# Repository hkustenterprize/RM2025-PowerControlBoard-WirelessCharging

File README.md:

<div align="center">

# RM2025-超级电容与无线充电系统开源
## 香港科技大学ENTERPRIZE战队

</div>

> 论坛链接：https://bbs.robomaster.com/article/761385?source=8

以下为复制论坛内容

大家好呀，RM2025的超级电容和无线充电的开源报告终于写完了，这套前前后后做了三四个月，最后在用在了所有上场的车上（无线充只有步兵和英雄有），场上没出过什么问题，很稳定。硬件上与上一代开源没有很大变动，主要的改动是超级电容换了**峰值电流内环**，然后与无线充电进行了融合，放到了一个MCU上去控。虽然有一些缺陷和不足但是总体效果还可以，希望可以帮到大家。如果大家有任何有疑问或者发现有问题的地方欢迎随时联系！

> 欢迎加入开源交流QQ群：581184202

发射端/功控板硬件、功控板代码：xzm
> 联系方式：微信 xianziming0531，邮箱 zxianaa@connect.ust.hk

发射端代码：zzy
> 联系方式：微信 baoqi-zhong，邮箱 zzhongas@connect.ust.hk

## 前言

因为峰值电流调试起来比较复杂，也比较麻烦，所以大家有需要还是建议优先参考我们24年/23年的开源，这两版电容都是可以保证稳定的，24年的开源基本上板子做出了烧个代码就能用了。

硬件上整体改动不大，也是分了上下板的设计，下板加了一个用来无线充电的数控Buck，MCU换成了G474，为了峰值电流改了采样电阻的位置，然后根据写23赛季开源的学长的建议改了一下实现上管常开的方式，具体的东西都写在开源报告里了。

整体上场的效果还是不错的，电容响应很快，无线充电功率传输和反向通讯表现也很稳定（可惜复活赛输太快了没在比赛时充），今后有机会也会补充更多资料。无线充效果展示可以看 https://bbs.robomaster.com/article/760961 里面的视频。

## 工程文件

使用 KiCAD 8.0设计，可以点击下面的链接用 kicanvas 在线预览。

功控板上板：[<u>**点击预览**</u>](https://kicanvas.org/?github=https%3A%2F%2Fgithub.com%2Fhkustenterprize%2FRM2025-PowerControlBoard-WirelessCharging%2Ftree%2Fmain%2FPowerControl_PCM_V0.1_Control)

功控板下板： [<u>**点击预览**</u>](https://kicanvas.org/?github=https%3A%2F%2Fgithub.com%2Fhkustenterprize%2FRM2025-PowerControlBoard-WirelessCharging%2Ftree%2Fmain%2FPowerControl_PCM_V0.1_Power )

无线充电发射端： [<u>**点击预览**</u>](https://kicanvas.org/?github=https%3A%2F%2Fgithub.com%2Fhkustenterprize%2FRM2025-PowerControlBoard-WirelessCharging%2Ftree%2Fmain%2FWirelessCharger_V0.1 )

无线充电接收端线圈： [<u>**点击预览**</u>](https://kicanvas.org/?github=https%3A%2F%2Fgithub.com%2Fhkustenterprize%2FRM2025-PowerControlBoard-WirelessCharging%2Ftree%2Fmain%2FPowerControlBoard_RXCoil_V0.1 )

## 开源报告

见“技术报告” 文件夹

[**技术报告 PDF**](https://github.com/hkustenterprize/RM2025-PowerControlBoard-WirelessCharging/blob/main/%E6%8A%80%E6%9C%AF%E6%8A%A5%E5%91%8A/RM2025%E8%B6%85%E7%BA%A7%E7%94%B5%E5%AE%B9%E4%B8%8E%E6%97%A0%E7%BA%BF%E5%85%85%E7%94%B5%E7%B3%BB%E7%BB%9F%E6%8A%80%E6%9C%AF%E6%8A%A5%E5%91%8A.pdf)

[**省流版 PDF**](https://github.com/hkustenterprize/RM2025-PowerControlBoard-WirelessCharging/blob/main/%E6%8A%80%E6%9C%AF%E6%8A%A5%E5%91%8A/%E7%9C%81%E6%B5%81%E7%89%88.pdf)

## 代码

功控板（超级电容+无线充电接收端）：待整理和测试，9月初整理过后的代码测好后开源

无线充电发射端：待整理，近期开源

## 相关开源
无线充电站机械结构：[ **【RM2025-无线充电站机械结构思路分享】香港科技大学ENTERPRIZE战队** ](https://bbs.robomaster.com/article/760961)

电容组：[**【RM2025-超小体积1980J电容组开源】香港科技大学ENTERPRIZE战队**](https://bbs.robomaster.com/article/760959)

## 复刻/已知问题/使用注意事项

1. 如果使用无线充电需要在功率控制板下板 无线充Buck的上管并联一个大功率肖特基二极管
2. 无线充电发射端的峰值检测二极管需要替换为肖特基二极管并联或其他快恢复二极管
3. 无线充电发射端的谐振电感需要自己绕，铁粉芯磁芯+利兹线
4. 使用手册和其他注意事项待完善，如遇问题欢迎随时联系

## 参考资料
1. 【RM2024超级电容控制器硬件+软件完全开源】 (史上最详细的开源！)香港科技大学ENTERPRIZE战队 https://bbs.robomaster.com/article/54127

2. 【RM2023-数控超级电容方案开源】香港科技大学-ENTERPRIZE战队 https://bbs.robomaster.com/article/9452

3. STM32 AN5306: Operational Amplifier (OPAMP) usage in STM32G4 Series

4. STM32 RM0440: STM32G4 series advanced Arm®-based 32-bit MCUs

5. STM32 AN5497: Introduction to the buck current mode with the B-G474E-DPOW1 Discovery kit（重要）

6. STM32 AN4539: HRTIM cookbook 

7. Qi Specification: Communications Physical Layer, Version 2.0 April 2023 

8. NXP AN4701: Demodulating Communication Signals of Qi-Compliant Low-Power Wireless Charger Using MC56F8006 DSC
STM32G474xB STM32G474xC STM32G474xE Datasheet 

## 致谢
感谢 ENTERPRIZE 战队硬件组学长 JYC RY OFR 为硬件部门打下的坚实基础，并在本赛季为超级电容与无线充电系统的设计调试中提供了巨大帮助

感谢 ENTERPRIZE 战队硬件组队员 ZZY 承担了大部分构建、调试发射端代码的工作

感谢机械组SJY帮忙画的保护外壳

感谢吉林大学、中国石油大学（华东）、华南理工大学在交流中分享的宝贵经验

非常感谢各位对香港科技大学 ENTERPRIZE 战队开源项目的关注与支持，若您在机器人设计过程中受益于我们的项目，恳请在开源引用中注明我们的项目来源。你们的支持是我们不断前行的动力。让我们携手共建一个鼓励创新、协作与超越的 RM 开源生态。

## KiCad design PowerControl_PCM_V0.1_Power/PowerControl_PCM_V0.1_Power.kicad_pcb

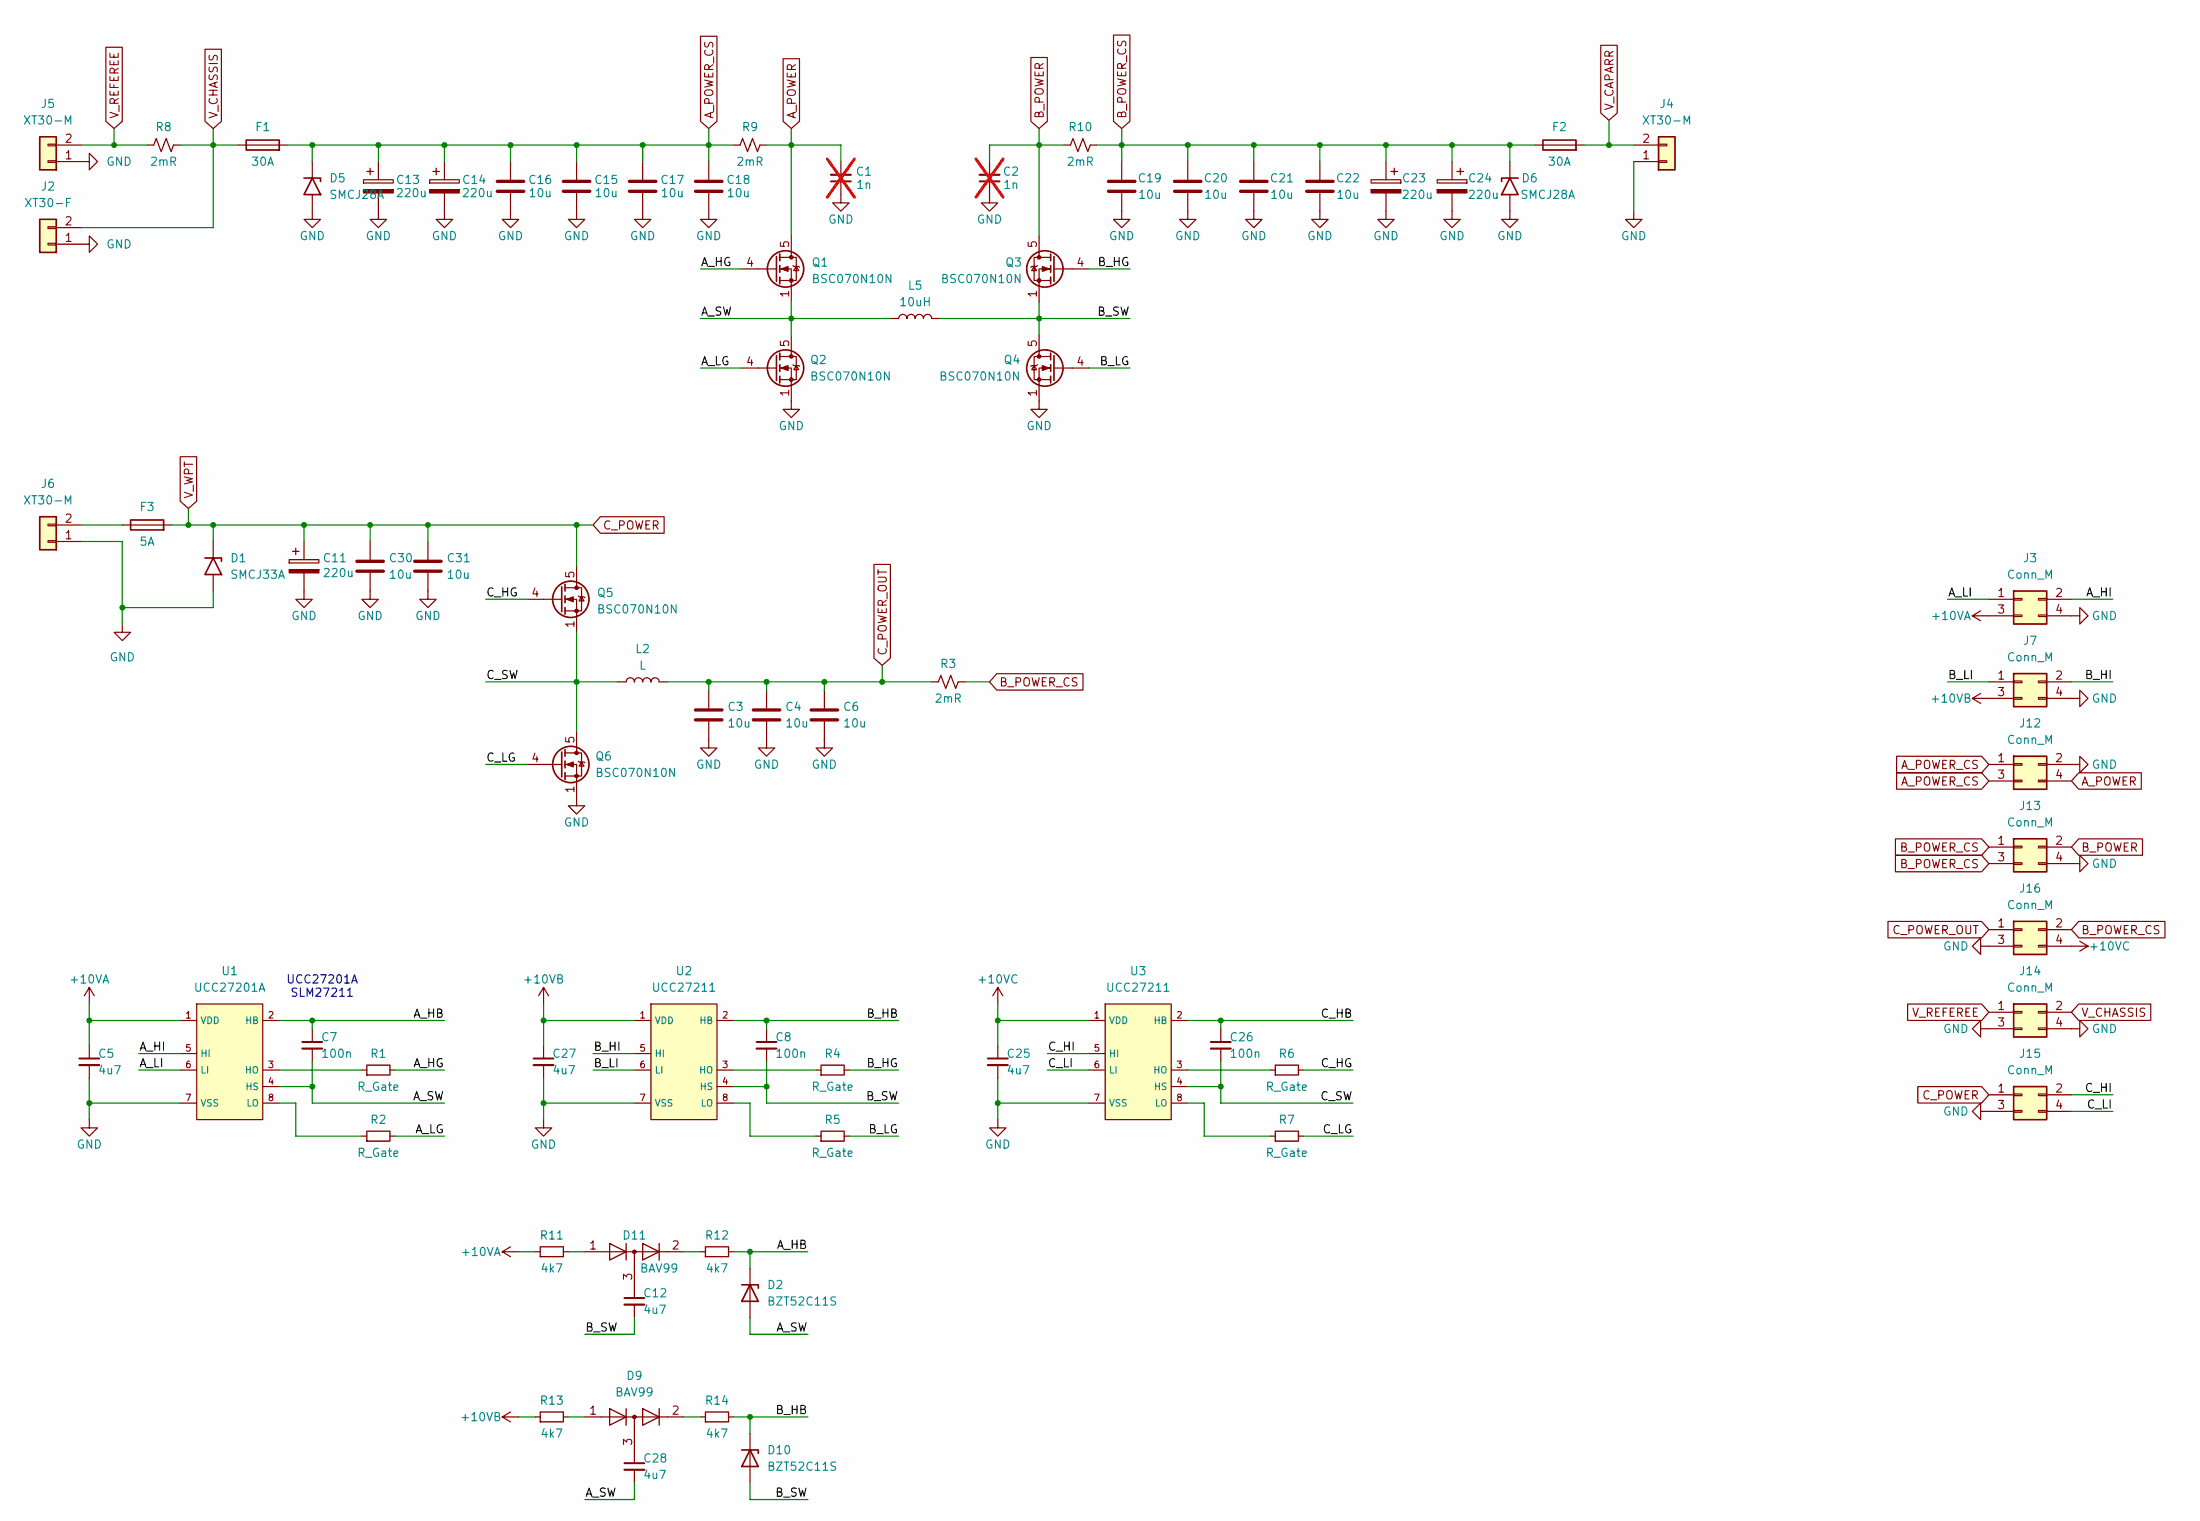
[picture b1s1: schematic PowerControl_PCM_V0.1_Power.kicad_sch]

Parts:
C1, C2: 1n; C_0603_1608Metric; not fitted
C3, C4, C6, C15, C16, C17, C18, C19, C20, C21, C22, C30, C31: 10u; C_1206_3216Metric
C5, C12, C25, C27, C28: 4u7; C_0603_1608Metric
C7, C8, C26: 100n; C_0603_1608Metric
C11, C13, C14, C23, C24: 220u; C_D8.0mm_P3.50mm
D1: SMCJ33A; D_SMC
D2, D10: BZT52C11S; D_SOD-323_HandSoldering
D5, D6: SMCJ28A; D_SMC
D9, D11: BAV99; SOT-23
F1, F2: 30A; Fuse_Littelfuse-NANO2-451_453
F3: 5A; Fuse_Littelfuse-NANO2-451_453
J2: XT30-F; AMASS_XT30U-F_1x02_P5.0mm_Vertical
J3, J7, J12, J13, J14, J15, J16: Conn_M; PinHeader_2x02_P2.00mm_Vertical_SMD
J4, J5, J6: XT30-M; AMASS_XT30U-M_1x02_P5.0mm_Vertical
L2: L; L_Wuerth_HCI-1040
L5: 10uH; L_VER2923
Q1, Q2, Q3, Q4, Q5, Q6: BSC070N10N; TDSON-8-1
R1, R2, R4, R5, R6, R7: R_Gate; R_0603_1608Metric
R3, R8, R9, R10: 2mR; R_2512_6332Metric
R11, R12, R13, R14: 4k7; R_0603_1608Metric
U1: UCC27201A; SOIC-8_3.9x4.9mm_P1.27mm
U2, U3: UCC27211; SOIC-8_3.9x4.9mm_P1.27mm

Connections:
+10VA: C5.1, J3.3, R11.1, U1.1 (VDD)
+10VB: C27.1, J7.3, R13.1, U2.1 (VDD)
+10VC: C25.1, J16.4, U3.1 (VDD)
/A_HB: C7.1, D2.1 (K), R12.2, U1.2 (HB)
/A_HG: Q1.4 (G), R1.2
/A_HI: J3.2, U1.5 (HI)
/A_LG: Q2.4 (G), R2.2
/A_LI: J3.1, U1.6 (LI)
/A_SW: C7.2, C28.2, D2.2 (A), L5.1, Q1.1 (S), Q1.2 (S), Q1.3 (S), Q2.5 (D), U1.4 (HS)
/B_HB: C8.1, D10.1 (K), R14.2, U2.2 (HB)
/B_HG: Q3.4 (G), R4.2
/B_HI: J7.2, U2.5 (HI)
/B_LG: Q4.4 (G), R5.2
/B_LI: J7.1, U2.6 (LI)
/B_SW: C8.2, C12.2, D10.2 (A), L5.2, Q3.1 (S), Q3.2 (S), Q3.3 (S), Q4.5 (D), U2.4 (HS)
/C_HB: C26.1, U3.2 (HB)
/C_HG: Q5.4 (G), R6.2
/C_HI: J15.2, U3.5 (HI)
/C_LG: Q6.4 (G), R7.2
/C_LI: J15.4, U3.6 (LI)
/C_SW: C26.2, L2.1, Q5.1 (S), Q5.2 (S), Q5.3 (S), Q6.5 (D), U3.4 (HS)
A_POWER: C1.2, J12.4, Q1.5 (D), R9.2
A_POWER_CS: C13.1, C14.1, C15.2, C16.2, C17.2, C18.2, D5.1 (A1), F1.2, J12.1, J12.3, R9.1
B_POWER: C2.2, J13.2, Q3.5 (D), R10.1
B_POWER_CS: C19.2, C20.2, C21.2, C22.2, C23.1, C24.1, D6.1 (A1), F2.1, J13.1, J13.3, J16.2, R3.2, R10.2
C_POWER: C11.1, C30.1, C31.1, D1.1 (A1), F3.2, J15.1, Q5.5 (D)
C_POWER_OUT: C3.1, C4.1, C6.1, J16.1, L2.2, R3.1
GND: C1.1, C2.1, C3.2, C4.2, C5.2, C6.2, C11.2, C13.2, C14.2, C15.1, C16.1, C17.1, C18.1, C19.1, C20.1, C21.1, C22.1, C23.2, C24.2, C25.2, C27.2, C30.2, C31.2, D1.2 (A2), D5.2 (A2), D6.2 (A2), J2.1, J3.4, J4.1, J5.1, J6.1, J7.4, J12.2, J13.4, J14.3, J14.4, J15.3, J16.3, Q2.1 (S), Q2.2 (S), Q2.3 (S), Q4.1 (S), Q4.2 (S), Q4.3 (S), Q6.1 (S), Q6.2 (S), Q6.3 (S), U1.7 (VSS), U2.7 (VSS), U3.7 (VSS)
unnamed: C12.1, D11.3 (K)
unnamed: C28.1, D9.3 (K)
unnamed: D9.2 (A), R14.1
unnamed: D9.1 (K), R13.2
unnamed: D11.2 (A), R12.1
unnamed: D11.1 (K), R11.2
unnamed: F3.1, J6.2
unnamed: R1.1, U1.3 (HO)
unnamed: R2.1, U1.8 (LO)
unnamed: R4.1, U2.3 (HO)
unnamed: R5.1, U2.8 (LO)
unnamed: R6.1, U3.3 (HO)
unnamed: R7.1, U3.8 (LO)
V_CAPARR: F2.2, J4.2
V_CHASSIS: F1.1, J2.2, J14.2, R8.2
V_REFEREE: J5.2, J14.1, R8.1

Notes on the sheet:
UCC27201A SLM27211

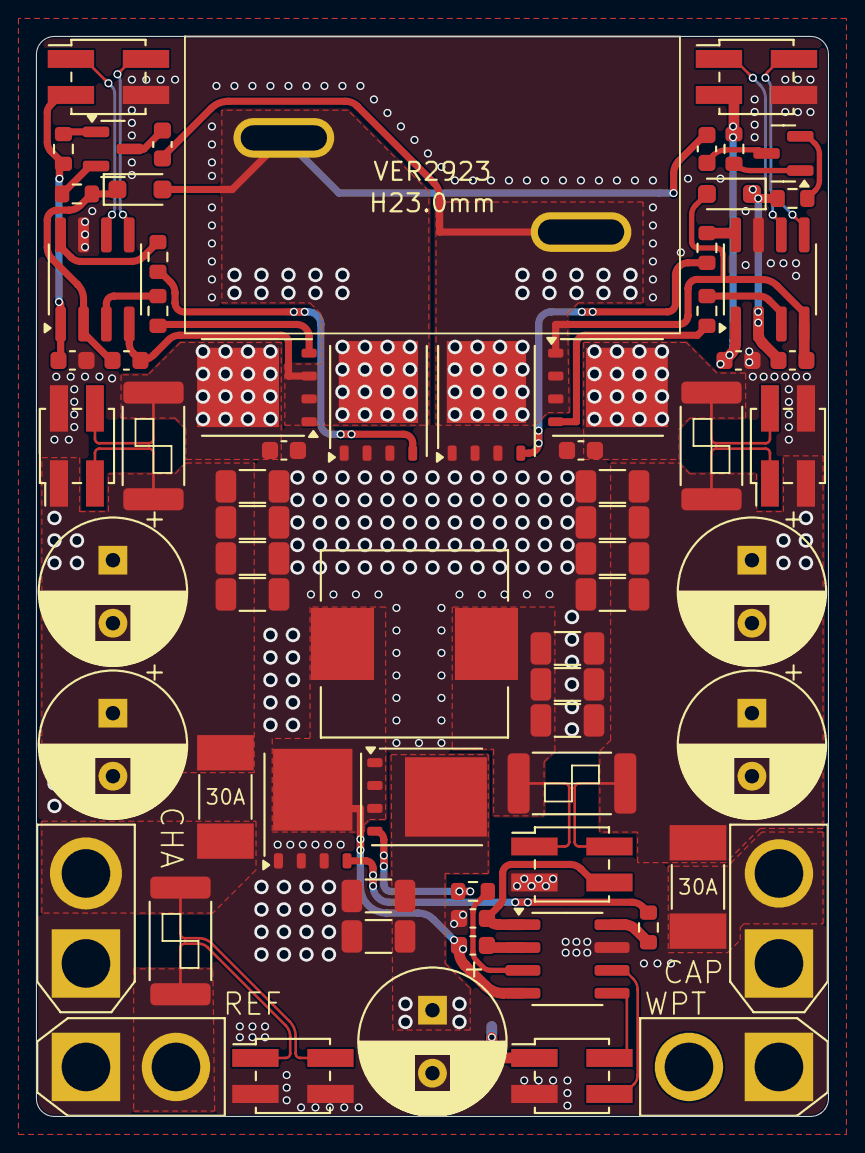
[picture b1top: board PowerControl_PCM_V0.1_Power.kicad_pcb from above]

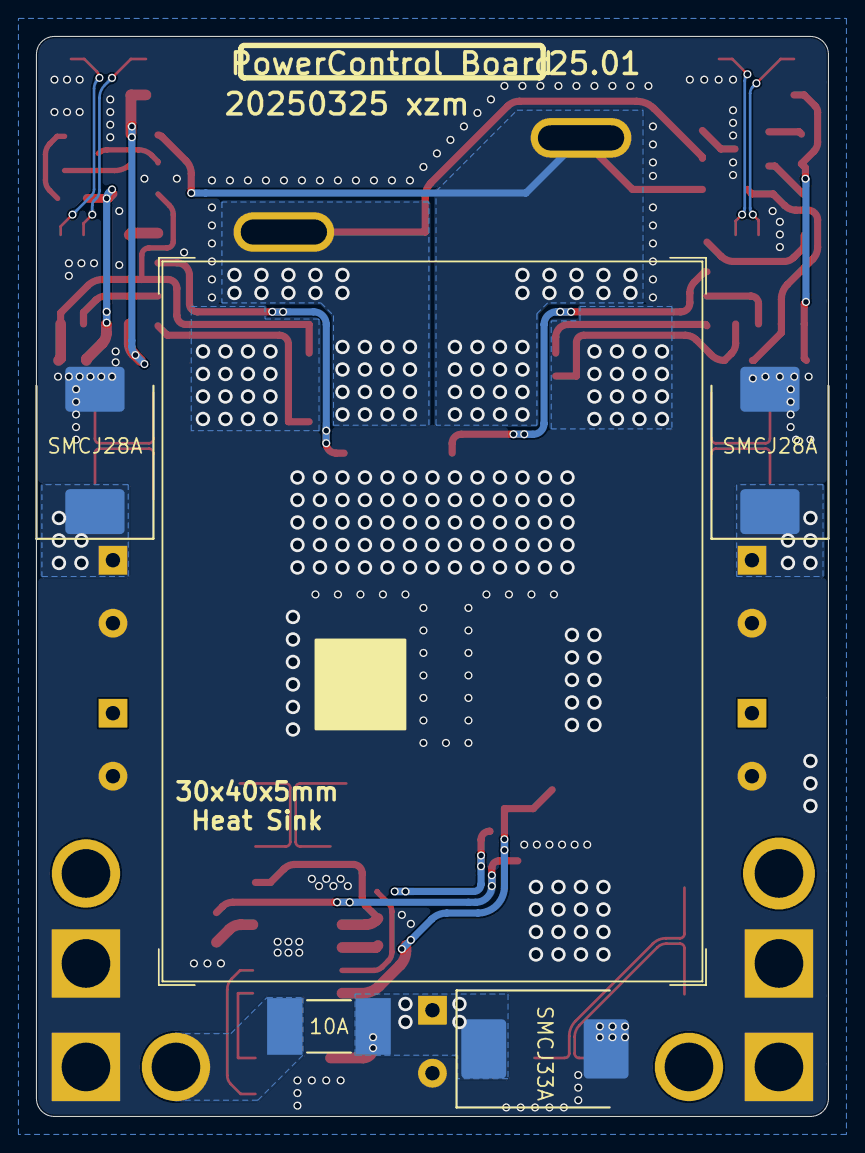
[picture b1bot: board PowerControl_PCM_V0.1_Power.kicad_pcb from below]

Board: 2 copper layers, 44.0 x 60.0 mm, 74 parts (4 on the bottom side), 44 nets.

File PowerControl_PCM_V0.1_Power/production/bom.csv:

Designator,Footprint,Quantity,Value,LCSC Part #
"C1, C2",0603,2,1n,
"C11, C13, C14, C23, C24",C_D8.0mm_P3.50mm,5,220u,
"C12, C25, C27, C28, C5",0603,5,4u7,
"C15, C16, C17, C18, C19, C20, C21, C22, C3, C30, C31, C4, C6",1206,13,10u,
"C26, C7, C8",0603,3,100n,
D1,D_SMC,1,SMCJ33A,
"D10, D2",D_SOD-323_HandSoldering,2,BZT52C11S,
"D11, D9",SOT-23,2,BAV99,
"D5, D6",D_SMC,2,SMCJ28A,
"F1, F2",Fuse_Littelfuse-NANO2-451_453,2,30A,
F3,Fuse_Littelfuse-NANO2-451_453,1,5A,
"J12, J13, J14, J15, J16, J3, J7",PinHeader_2x02_P2.00mm_Vertical_SMD,7,Conn_M,
J2,AMASS_XT30U-F_1x02_P5.0mm_Vertical,1,XT30-F,
"J4, J5, J6",AMASS_XT30U-M_1x02_P5.0mm_Vertical,3,XT30-M,
L2,L_Wuerth_HCI-1040,1,L,
L5,L_VER2923,1,10uH,
"Q1, Q2, Q3, Q4, Q5, Q6",TDSON-8-1,6,BSC070N10N,
"R1, R2, R4, R5, R6, R7",0603,6,R_Gate,
"R10, R3, R8, R9",2512,4,2mR,
"R11, R12, R13, R14",0603,4,4k7,
U1,SOIC-8_3.9x4.9mm_P1.27mm,1,UCC27201A,
"U2, U3",SOIC-8_3.9x4.9mm_P1.27mm,2,UCC27211,

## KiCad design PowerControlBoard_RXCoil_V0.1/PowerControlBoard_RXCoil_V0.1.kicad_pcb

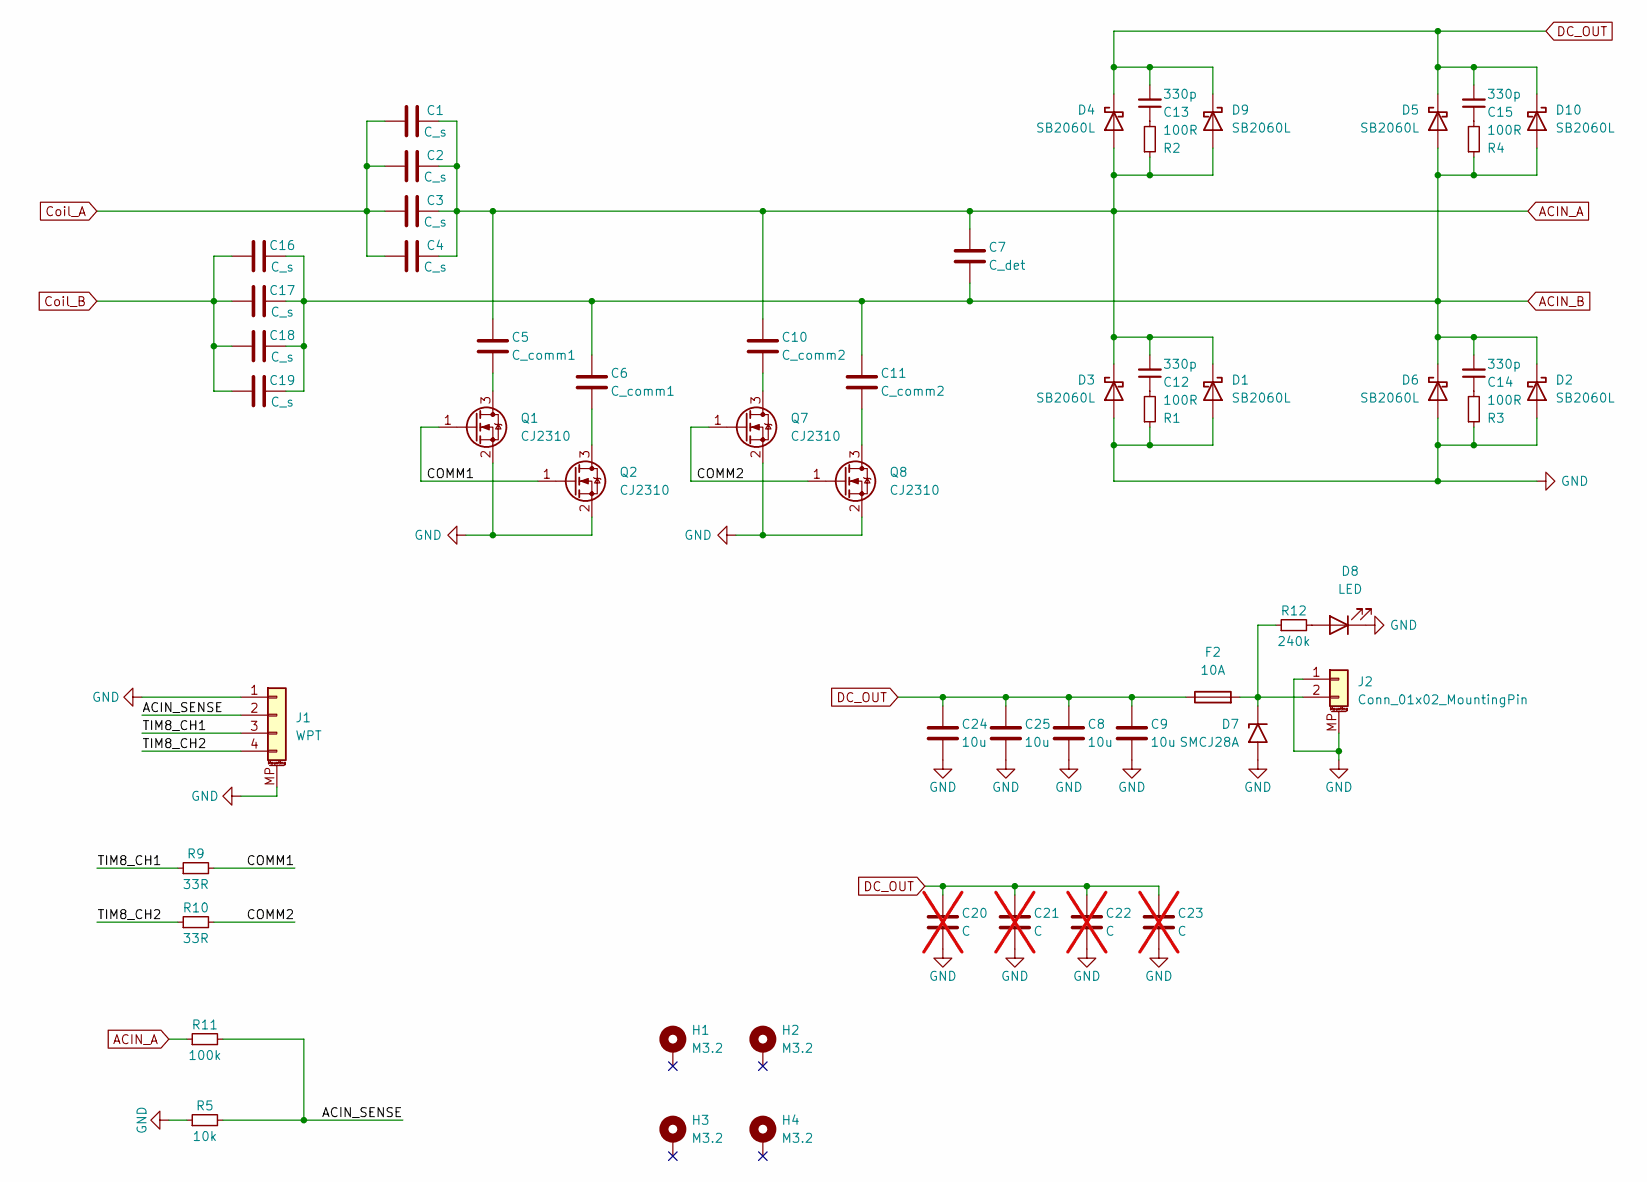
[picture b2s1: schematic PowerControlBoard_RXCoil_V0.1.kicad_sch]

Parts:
C1, C2, C3, C4, C16, C17, C18, C19: C_s; C_1206_3216Metric
C5, C6: C_comm1; C_1206_3216Metric
C7: C_det; C_1206_3216Metric
C8, C9, C24, C25: 10u; C_1206_3216Metric
C10, C11: C_comm2; C_1206_3216Metric
C12, C13, C14, C15: 330p; C_0603_1608Metric
C20, C21, C22, C23: C; C_1210_3225Metric; not fitted
D1, D2, D3, D4, D5, D6, D9, D10: SB2060L; D_PowerDI-5_3D
D7: SMCJ28A; D_SMC
D8: LED; LED_0603_1608Metric
F2: 10A; Fuseholder_Littelfuse_Nano2_157x
H1, H2, H3, H4: M3.2; MountingHole_3.2mm_M3_DIN965_Pad
J1: WPT; JST_GH_SM04B-GHS-TB_1x04-1MP_P1.25mm_Horizontal
J2: Conn_01x02_MountingPin; AMASS_XT30PW-F_Horizontal
Q1, Q2, Q7, Q8: CJ2310; SOT-23
R1, R2, R3, R4: 100R; R_0603_1608Metric
R5: 10k; R_0603_1608Metric
R9, R10: 33R; R_0603_1608Metric
R11: 100k; R_0603_1608Metric
R12: 240k; R_0603_1608Metric

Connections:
/ACIN_SENSE: J1.2, R5.2, R11.2
/COMM1: Q1.1 (G), Q2.1 (G), R9.2
/COMM2: Q7.1 (G), Q8.1 (G), R10.2
/TIM8_CH1: J1.3, R9.1
/TIM8_CH2: J1.4, R10.1
ACIN_A: C1.2, C2.2, C3.2, C4.2, C5.1, C7.1, C10.1, C12.2, D1.1 (K), D3.1 (K), D4.2 (A), D9.2 (A), R2.1, R11.1
ACIN_B: C6.1, C7.2, C11.1, C14.2, C16.2, C17.2, C18.2, C19.2, D2.1 (K), D5.2 (A), D6.1 (K), D10.2 (A), R4.1
Coil_A: C1.1, C2.1, C3.1, C4.1
Coil_B: C16.1, C17.1, C18.1, C19.1
DC_OUT: C8.1, C9.1, C13.2, C15.2, C20.1, C21.1, C22.1, C23.1, C24.1, C25.1, D4.1 (K), D5.1 (K), D9.1 (K), D10.1 (K), F2.1
GND: C8.2, C9.2, C20.2, C21.2, C22.2, C23.2, C24.2, C25.2, D1.2 (A), D2.2 (A), D3.2 (A), D6.2 (A), D7.2 (A2), D8.1 (K), J1.1, J1.MP (MountPin), J2.1, J2.MP (MountPin), Q1.2 (S), Q2.2 (S), Q7.2 (S), Q8.2 (S), R1.1, R3.1, R5.1
unnamed: C12.1, R1.2
unnamed: C13.1, R2.2
unnamed: C14.1, R3.2
unnamed: C15.1, R4.2
unnamed: D7.1 (A1), F2.2, J2.2, R12.1
unnamed: D8.2 (A), R12.2
unnamed: C5.2, Q1.3 (D)
unnamed: C6.2, Q2.3 (D)
unnamed: C10.2, Q7.3 (D)
unnamed: C11.2, Q8.3 (D)

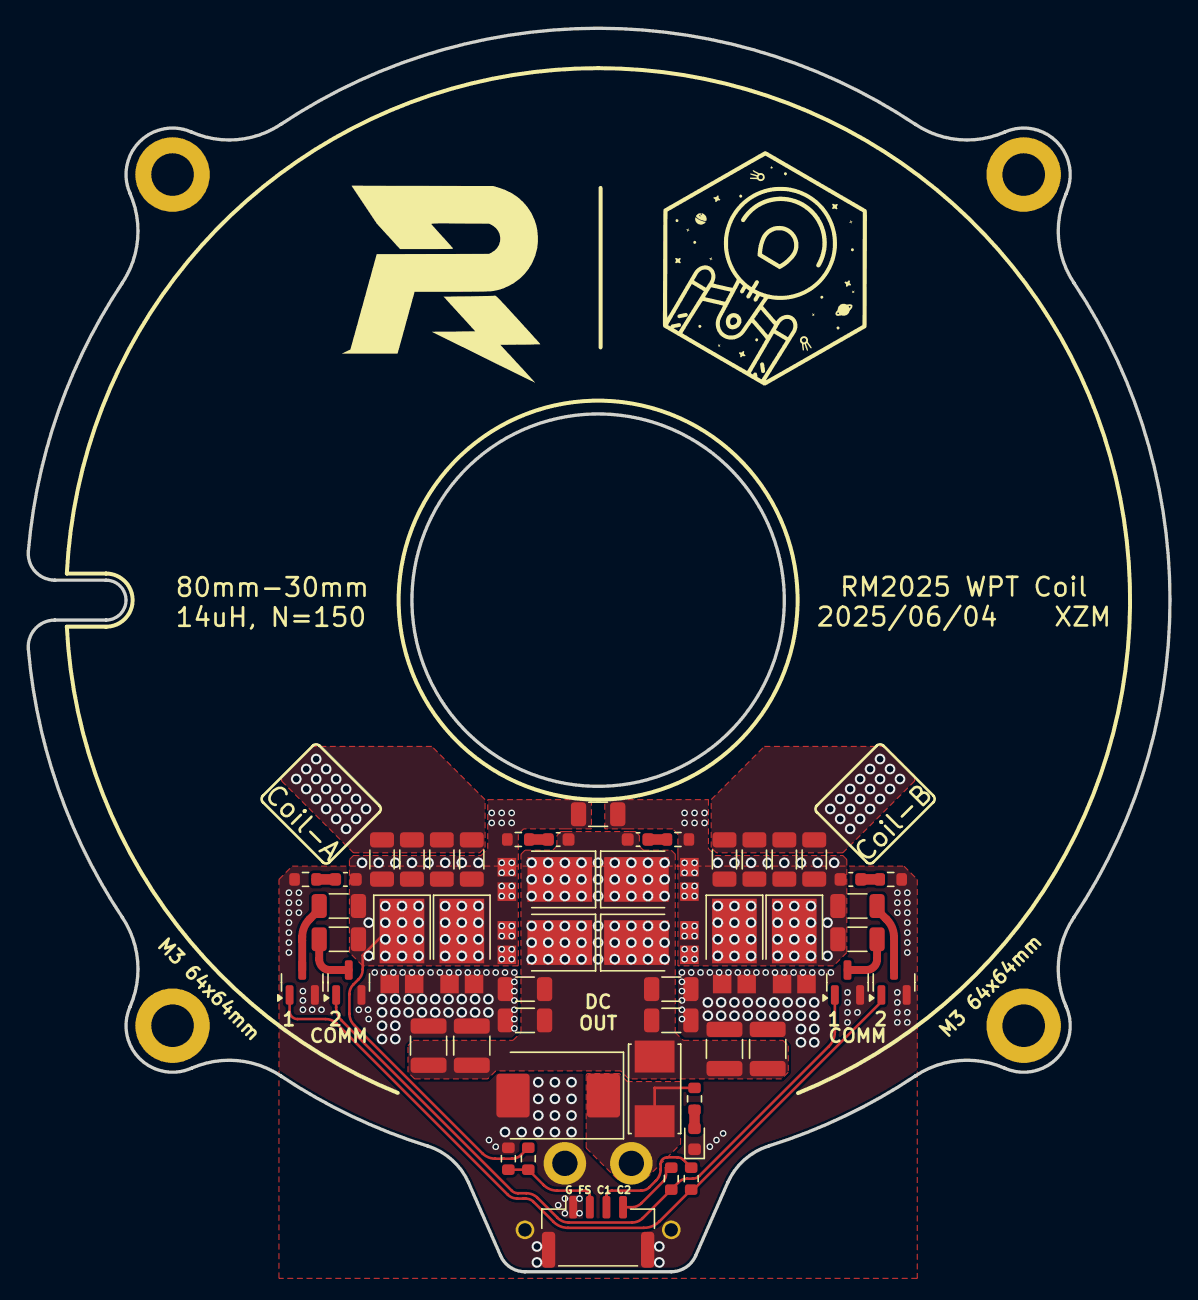
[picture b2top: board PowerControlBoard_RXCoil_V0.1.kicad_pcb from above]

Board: 2 copper layers, 85.8 x 93.5 mm, 55 parts (1 on the bottom side), 21 nets.

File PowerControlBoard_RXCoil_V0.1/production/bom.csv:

Designator,Footprint,Quantity,Value,LCSC Part #
"C1, C16, C17, C18, C19, C2, C3, C4",1206,8,C_s,
"C10, C11",1206,2,C_comm2,
"C12, C13, C14, C15",0603,4,330p,
"C20, C21, C22, C23",1210,4,C,
"C24, C25, C8, C9",1206,4,10u,
"C5, C6",1206,2,C_comm1,
C7,1206,1,C_det,
"D1, D10, D2, D3, D4, D5, D6, D9",D_PowerDI-5_3D,8,SB2060L,
D7,D_SMC,1,SMCJ28A,
D8,0603,1,LED,
F2,Fuseholder_Littelfuse_Nano2_157x,1,10A,
J1,JST_GH_SM04B-GHS-TB_1x04-1MP_P1.25mm_Horizontal,1,WPT,
J2,AMASS_XT30PW-F_Horizontal,1,Conn_01x02_MountingPin,
"Q1, Q2, Q7, Q8",SOT-23,4,CJ2310,
"R1, R2, R3, R4",0603,4,100R,
"R10, R9",0603,2,33R,
R11,0603,1,100k,
R12,0603,1,240k,
R5,0603,1,10k,

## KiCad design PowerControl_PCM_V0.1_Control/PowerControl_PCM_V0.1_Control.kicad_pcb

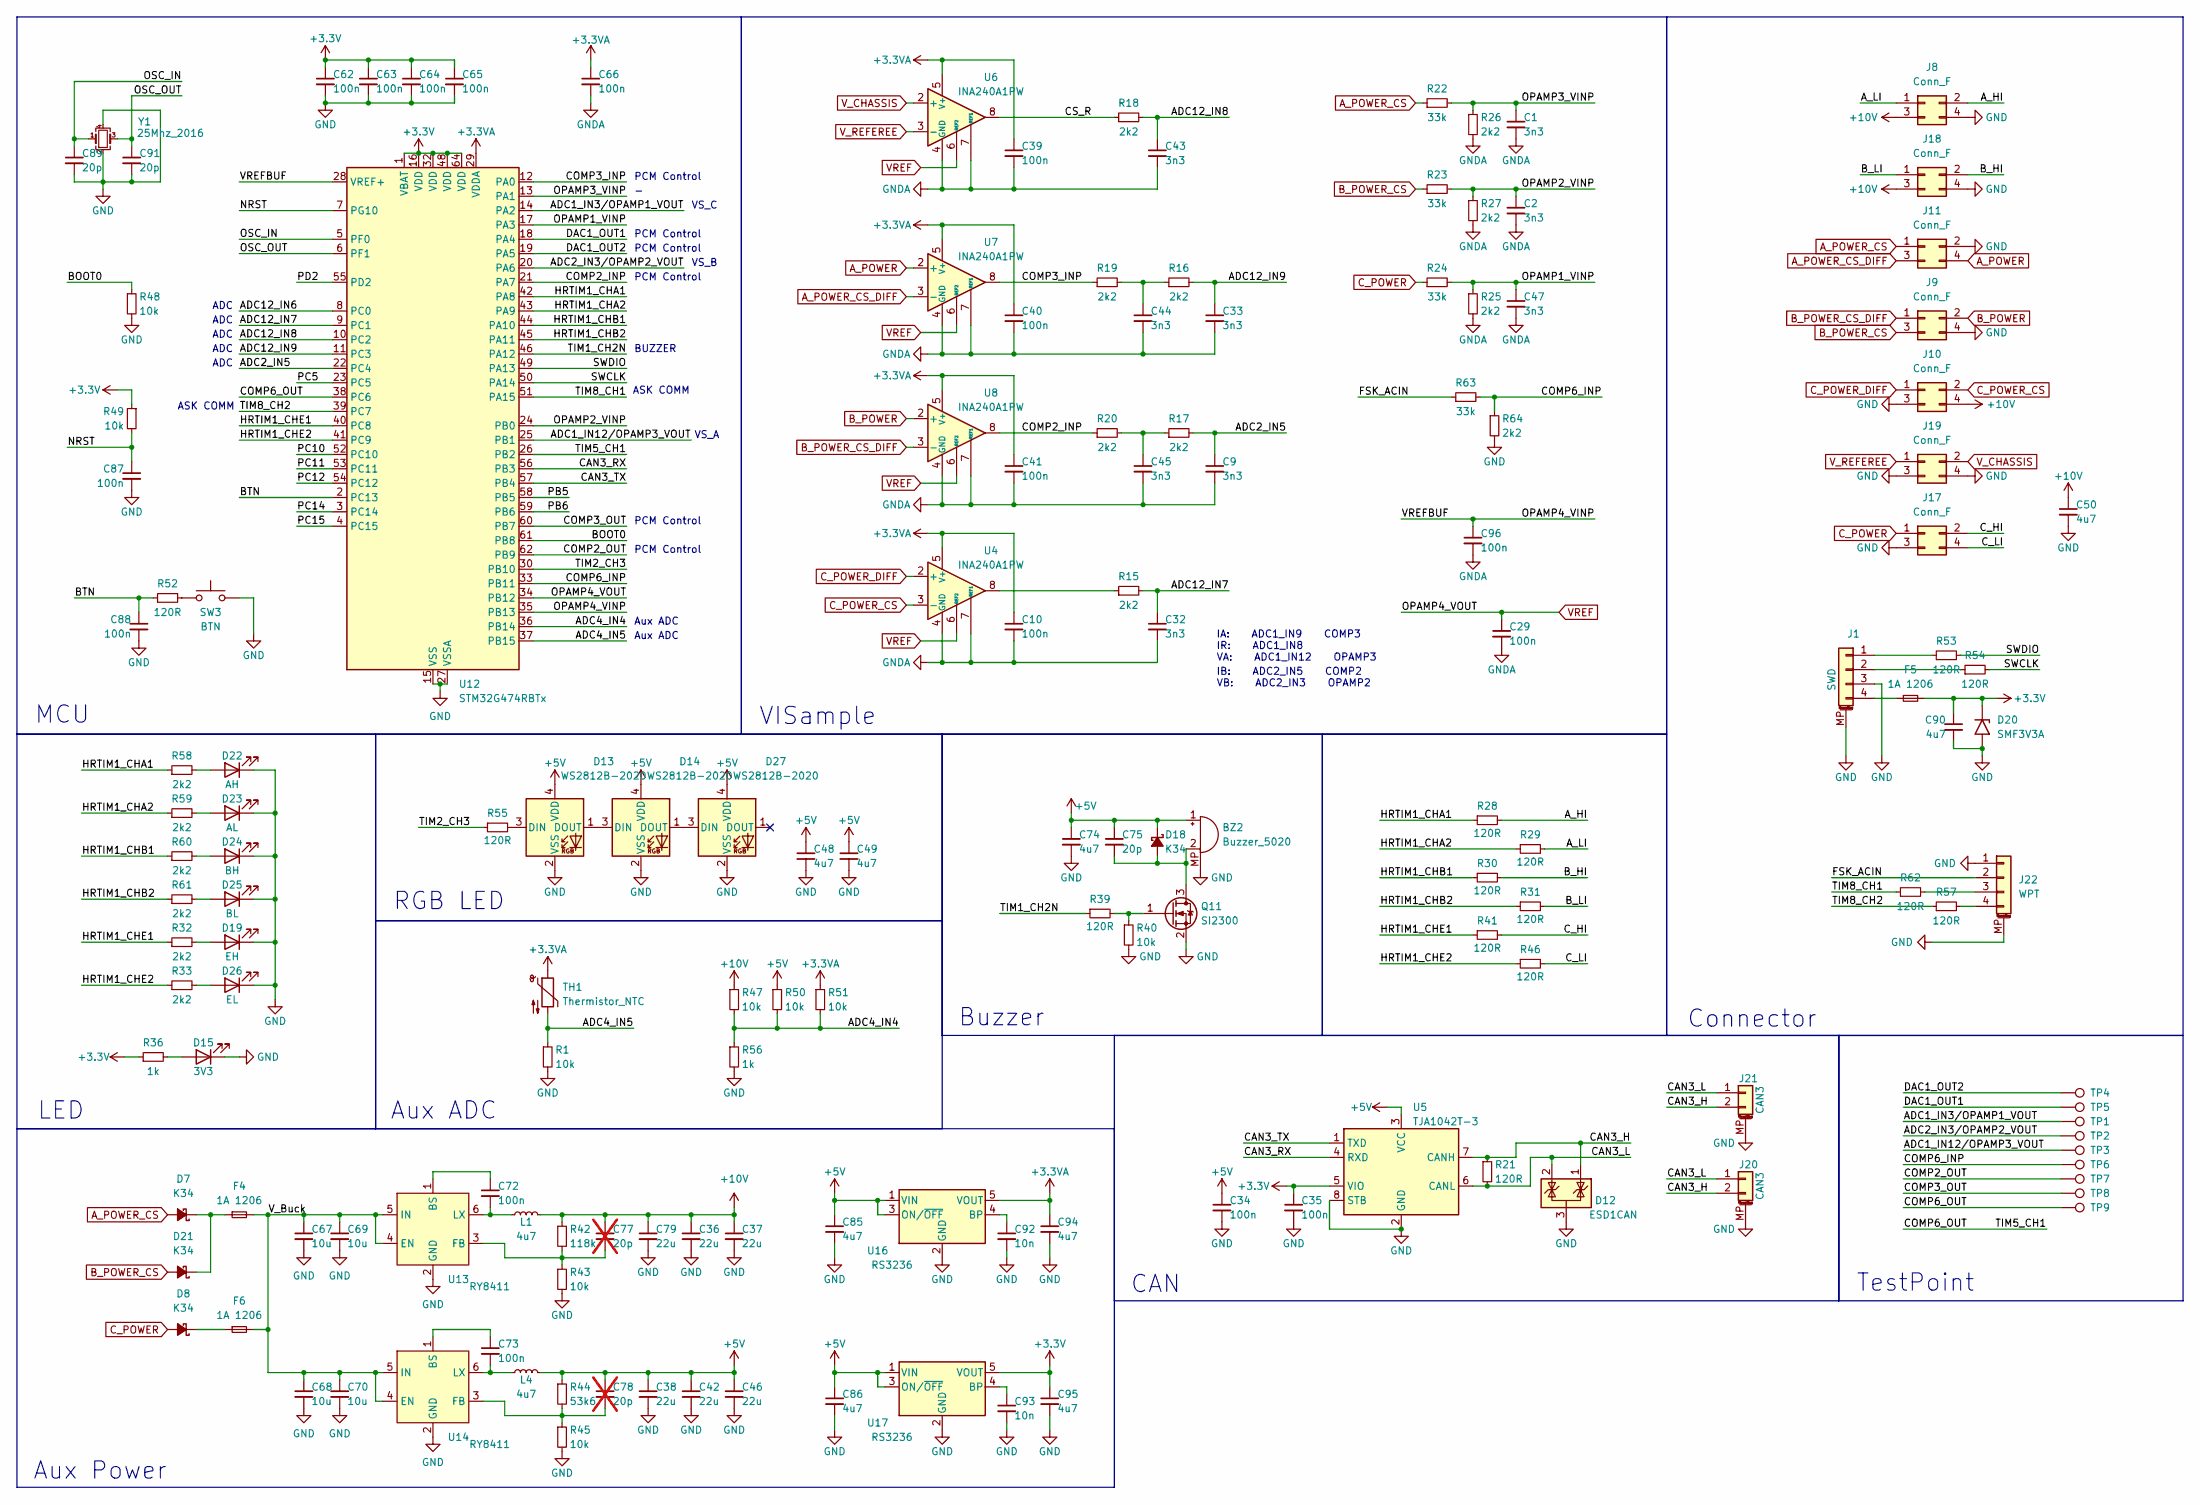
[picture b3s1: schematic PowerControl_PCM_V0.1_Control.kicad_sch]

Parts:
BZ2: Buzzer_5020
C1, C2, C9, C32, C33, C43, C44, C45, C47: 3n3; C_0603_1608Metric
C10, C29, C34, C35, C39, C40, C41, C62, C63, C64, C65, C66, C72, C73, C87, C88, C96: 100n; C_0603_1608Metric
C36, C37, C38, C42, C46, C79: 22u; C_0805_2012Metric
C48, C49, C50, C74, C85, C86, C90, C94, C95: 4u7; C_0603_1608Metric
C67, C68, C69, C70: 10u; C_1206_3216Metric
C75, C89, C91: 20p; C_0603_1608Metric
C77, C78: 20p; C_0603_1608Metric; not fitted
C92, C93: 10n; C_0603_1608Metric
D7, D8, D18, D21: K34; D_SMF
D12: ESD1CAN; SOT-23
D13, D14, D27: WS2812B-2020
D15: 3V3; LED_0603_1608Metric
D19: EH; LED_0603_1608Metric
D20: SMF3V3A; D_SMF
D22: AH; LED_0603_1608Metric
D23: AL; LED_0603_1608Metric
D24: BH; LED_0603_1608Metric
D25: BL; LED_0603_1608Metric
D26: EL; LED_0603_1608Metric
F4, F5, F6: 1A 1206; Fuse_1206_3216Metric
J1: SWD; Molex_PicoBlade_53261-0471_1x04-1MP_P1.25mm_Horizontal
J8, J9, J10, J11, J17, J18, J19: Conn_F; PinSocket_2x02_P2.00mm
J20, J21: CAN3; JST_GH_BM02B-GHS-TBT_1x02-1MP_P1.25mm_Vertical
J22: WPT; JST_GH_BM04B-GHS-TBT_1x04-1MP_P1.25mm_Vertical
L1, L4: 4u7; L_Sunlord_SWPA3015S
Q11: SI2300; SOT-23
R1, R40, R43, R45, R47, R48, R49, R50, R51: 10k; R_0603_1608Metric
R15, R16, R17, R18, R19, R20, R25, R26, R27, R32, R33, R58, R59, R60, R61, R64: 2k2; R_0603_1608Metric
R21, R28, R29, R30, R31, R39, R41, R46, R52, R53, R54, R55, R57, R62: 120R; R_0603_1608Metric
R22, R23, R24, R63: 33k; R_0603_1608Metric
R36, R56: 1k; R_0603_1608Metric
R42: 118k; R_0603_1608Metric
R44: 53k6; R_0603_1608Metric
SW3: BTN; Button_PTS810
TH1: Thermistor_NTC; R_0603_1608Metric
TP1, TP2, TP3, TP4, TP5, TP6, TP7, TP8, TP9: TestPoint; TestPoint_Pad_D1.0mm
U4, U6, U7, U8: INA240A1PW; TSSOP-8_4.4x3mm_P0.65mm
U5: TJA1042T-3; SOIC-8_3.9x4.9mm_P1.27mm
U12: STM32G474RBTx; LQFP-64_10x10mm_P0.5mm
U13, U14: RY8411; SOT-23-6
U16, U17: RS3236; SOT-23-5
Y1: 25Mhz_2016; Crystal_SMD_2016

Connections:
+3.3V: C35.1, C62.1, C63.1, C64.1, C65.1, C90.1, C95.1, D20.1 (A1), F5.2, R36.1, R49.1, U5.5 (VIO), U12.1 (VBAT), U12.16 (VDD), U12.32 (VDD), U12.48 (VDD), U12.64 (VDD), U17.5 (VOUT)
+3.3VA: C10.1, C39.1, C40.1, C41.1, C66.1, C94.1, R51.1, TH1.1, U4.5 (V+), U6.5 (V+), U7.5 (V+), U8.5 (V+), U12.29 (VDDA), U16.5 (VOUT)
+5V: BZ2.1 (+), C34.1, C38.1, C42.1, C46.1, C48.1, C49.1, C74.1, C75.1, C78.1, C85.1, C86.1, D13.4 (VDD), D14.4 (VDD), D18.1 (K), D27.4 (VDD), L4.2, R44.1, R50.1, U5.3 (VCC), U16.1 (VIN), U16.3 (ON/~OFF), U17.1 (VIN), U17.3 (ON/~OFF)
+10V: C36.1, C37.1, C50.1, C77.1, C79.1, J8.3, J10.4, J18.3, L1.2, R42.1, R47.1
/ADC1_IN3/OPAMP1_VOUT: TP1.1, U12.14 (PA2)
/ADC1_IN12/OPAMP3_VOUT: TP3.1, U12.25 (PB1)
/ADC2_IN3/OPAMP2_VOUT: TP2.1, U12.20 (PA6)
/ADC2_IN5: C9.1, R17.2, U12.22 (PC4)
/ADC4_IN4: R47.2, R50.2, R51.2, R56.1, U12.36 (PB14)
/ADC4_IN5: R1.1, TH1.2, U12.37 (PB15)
/ADC12_IN6: U12.8 (PC0)
/ADC12_IN7: C32.1, R15.2, U12.9 (PC1)
/ADC12_IN8: C43.1, R18.2, U12.10 (PC2)
/ADC12_IN9: C33.1, R16.2, U12.11 (PC3)
/A_HI: J8.2, R28.2
/A_LI: J8.1, R29.2
/BOOT0: R48.1, U12.61 (PB8)
/BTN: C88.1, R52.1, U12.2 (PC13)
/B_HI: J18.2, R30.2
/B_LI: J18.1, R31.2
/CAN3_H: D12.1 (K), J20.2, J21.2, R21.1, U5.7 (CANH)
/CAN3_L: D12.2 (K), J20.1, J21.1, R21.2, U5.6 (CANL)
/CAN3_RX: U5.4 (RXD), U12.56 (PB3)
/CAN3_TX: U5.1 (TXD), U12.57 (PB4)
/COMP2_INP: R20.1, U8.8, U12.21 (PA7)
/COMP2_OUT: TP7.1, U12.62 (PB9)
/COMP3_INP: R19.1, U7.8, U12.12 (PA0)
/COMP3_OUT: TP8.1, U12.60 (PB7)
/COMP6_INP: R63.2, R64.1, TP6.1, U12.33 (PB11)
/COMP6_OUT: TP9.1, U12.26 (PB2), U12.38 (PC6)
/CS_R: R18.1, U6.8
/C_HI: J17.2, R41.2
/C_LI: J17.4, R46.2
/DAC1_OUT1: TP5.1, U12.18 (PA4)
/DAC1_OUT2: TP4.1, U12.19 (PA5)
/FSK_ACIN: J22.2, R63.1
/HRTIM1_CHA1: R28.1, R58.1, U12.42 (PA8)
/HRTIM1_CHA2: R29.1, R59.1, U12.43 (PA9)
/HRTIM1_CHB1: R30.1, R60.1, U12.44 (PA10)
/HRTIM1_CHB2: R31.1, R61.1, U12.45 (PA11)
/HRTIM1_CHE1: R32.1, R41.1, U12.40 (PC8)
/HRTIM1_CHE2: R33.1, R46.1, U12.41 (PC9)
/NRST: C87.1, R49.2, U12.7 (PG10)
/OPAMP1_VINP: C47.1, R24.2, R25.1, U12.17 (PA3)
/OPAMP2_VINP: C2.1, R23.2, R27.1, U12.24 (PB0)
/OPAMP3_VINP: C1.1, R22.2, R26.1, U12.13 (PA1)
/OPAMP4_VINP: C96.1, U12.28 (VREF+), U12.35 (PB13)
/OSC_IN: C89.1, U12.5 (PF0), Y1.1
/OSC_OUT: C91.1, U12.6 (PF1), Y1.3
/PB5: U12.58 (PB5)
/PB6: U12.59 (PB6)
/PC5: U12.23 (PC5)
/PC10: U12.52 (PC10)
/PC11: U12.53 (PC11)
/PC12: U12.54 (PC12)
/PC14: U12.3 (PC14)
/PC15: U12.4 (PC15)
/PD2: U12.55 (PD2)
/SWCLK: R54.2, U12.50 (PA14)
/SWDIO: R53.2, U12.49 (PA13)
/TIM1_CH2N: R39.1, U12.46 (PA12)
/TIM2_CH3: R55.1, U12.30 (PB10)
/TIM8_CH1: R62.1, U12.51 (PA15)
/TIM8_CH2: R57.1, U12.39 (PC7)
/V_Buck: C67.1, C68.1, C69.1, C70.1, F4.2, F6.2, U13.4 (EN), U13.5 (IN), U14.4 (EN), U14.5 (IN)
A_POWER: J11.4, U7.2 (+)
A_POWER_CS: D7.2 (A), J11.1, R22.1
A_POWER_CS_DIFF: J11.3, U7.3 (-)
B_POWER: J9.2, U8.2 (+)
B_POWER_CS: D21.2 (A), J9.3, R23.1
B_POWER_CS_DIFF: J9.1, U8.3 (-)
C_POWER: D8.2 (A), J17.1, R24.1
C_POWER_CS: J10.2, U4.3 (-)
C_POWER_DIFF: J10.1, U4.2 (+)
GND: BZ2.MP, C34.2, C35.2, C36.2, C37.2, C38.2, C42.2, C46.2, C48.2, C49.2, C50.2, C62.2, C63.2, C64.2, C65.2, C67.2, C68.2, C69.2, C70.2, C74.2, C79.2, C85.2, C86.2, C87.2, C88.2, C89.2, C90.2, C91.2, C92.2, C93.2, C94.2, C95.2, D12.3 (A), D13.2 (VSS), D14.2 (VSS), D15.1 (K), D19.1 (K), D20.2 (A2), D22.1 (K), D23.1 (K), D24.1 (K), D25.1 (K), D26.1 (K), D27.2 (VSS), J1.3, J1.MP (MountPin), J8.4, J9.4, J10.3, J11.2, J17.3, J18.4, J19.3, J19.4, J20.MP (MountPin), J21.MP (MountPin), J22.1, J22.MP (MountPin), Q11.2 (S), R1.2, R40.2, R43.2, R45.2, R48.2, R56.2, R64.2, SW3.2, U5.2 (GND), U5.8 (STB), U12.15 (VSS), U12.27 (VSSA), U12.31 (VSS), U12.47 (VSS), U12.63 (VSS), U13.2 (GND), U14.2 (GND), U16.2 (GND), U17.2 (GND), Y1.2, Y1.4
GNDA: C1.2, C2.2, C9.2, C10.2, C29.2, C32.2, C33.2, C39.2, C40.2, C41.2, C43.2, C44.2, C45.2, C47.2, C66.2, C96.2, R25.2, R26.2, R27.2, U4.1 (GND), U4.4 (GND), U4.7 (REF1), U6.1 (GND), U6.4 (GND), U6.7 (REF1), U7.1 (GND), U7.4 (GND), U7.7 (REF1), U8.1 (GND), U8.4 (GND), U8.7 (REF1)
unnamed: BZ2.2 (-), C75.2, D18.2 (A), Q11.3 (D)
unnamed: C44.1, R16.1, R19.2
unnamed: C45.1, R17.1, R20.2
unnamed: D8.1 (K), F6.1
unnamed: D13.3 (DIN), R55.2
unnamed: D13.1 (DOUT), D14.3 (DIN)
unnamed: D14.1 (DOUT), D27.3 (DIN)
unnamed: D15.2 (A), R36.2
unnamed: D19.2 (A), R32.2
unnamed: D7.1 (K), D21.1 (K), F4.1
unnamed: D22.2 (A), R58.2
unnamed: D23.2 (A), R59.2
unnamed: D24.2 (A), R60.2
unnamed: D25.2 (A), R61.2
unnamed: D26.2 (A), R33.2
unnamed: J1.1, R53.1
unnamed: J1.2, R54.1
unnamed: F5.1, J1.4
unnamed: J22.3, R62.2
unnamed: J22.4, R57.2
unnamed: Q11.1 (G), R39.2, R40.1
unnamed: R15.1, U4.8
unnamed: R52.2, SW3.1
unnamed: C72.1, U13.1 (BS)
unnamed: C77.2, R42.2, R43.1, U13.3 (FB)
unnamed: C72.2, L1.1, U13.6 (LX)
unnamed: C73.1, U14.1 (BS)
unnamed: C78.2, R44.2, R45.1, U14.3 (FB)
unnamed: C73.2, L4.1, U14.6 (LX)
unnamed: C92.1, U16.4 (BP)
unnamed: C93.1, U17.4 (BP)
VREF: C29.1, U4.6 (REF2), U6.6 (REF2), U7.6 (REF2), U8.6 (REF2), U12.34 (PB12)
V_CHASSIS: J19.2, U6.2 (+)
V_REFEREE: J19.1, U6.3 (-)

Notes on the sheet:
Aux ADC
VS_A
ADC
IA: ADC1_IN9 COMP3 IR: ADC1_IN8 VA: ADC1_IN12 OPAMP3
PCM Control
Buzzer
TestPoint
CAN
Connector
VS_C
BUZZER
VISample
IB: ADC2_IN5 COMP2 VB: ADC2_IN3 OPAMP2
ASK COMM
LED
RGB LED
Aux Power
VS_B
MCU
